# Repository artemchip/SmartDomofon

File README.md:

# Умная абонентская трубка для аналоговых домофонов
Авто-открытие, воспроизведение аудио в линию вызова
Устройство:

UI:

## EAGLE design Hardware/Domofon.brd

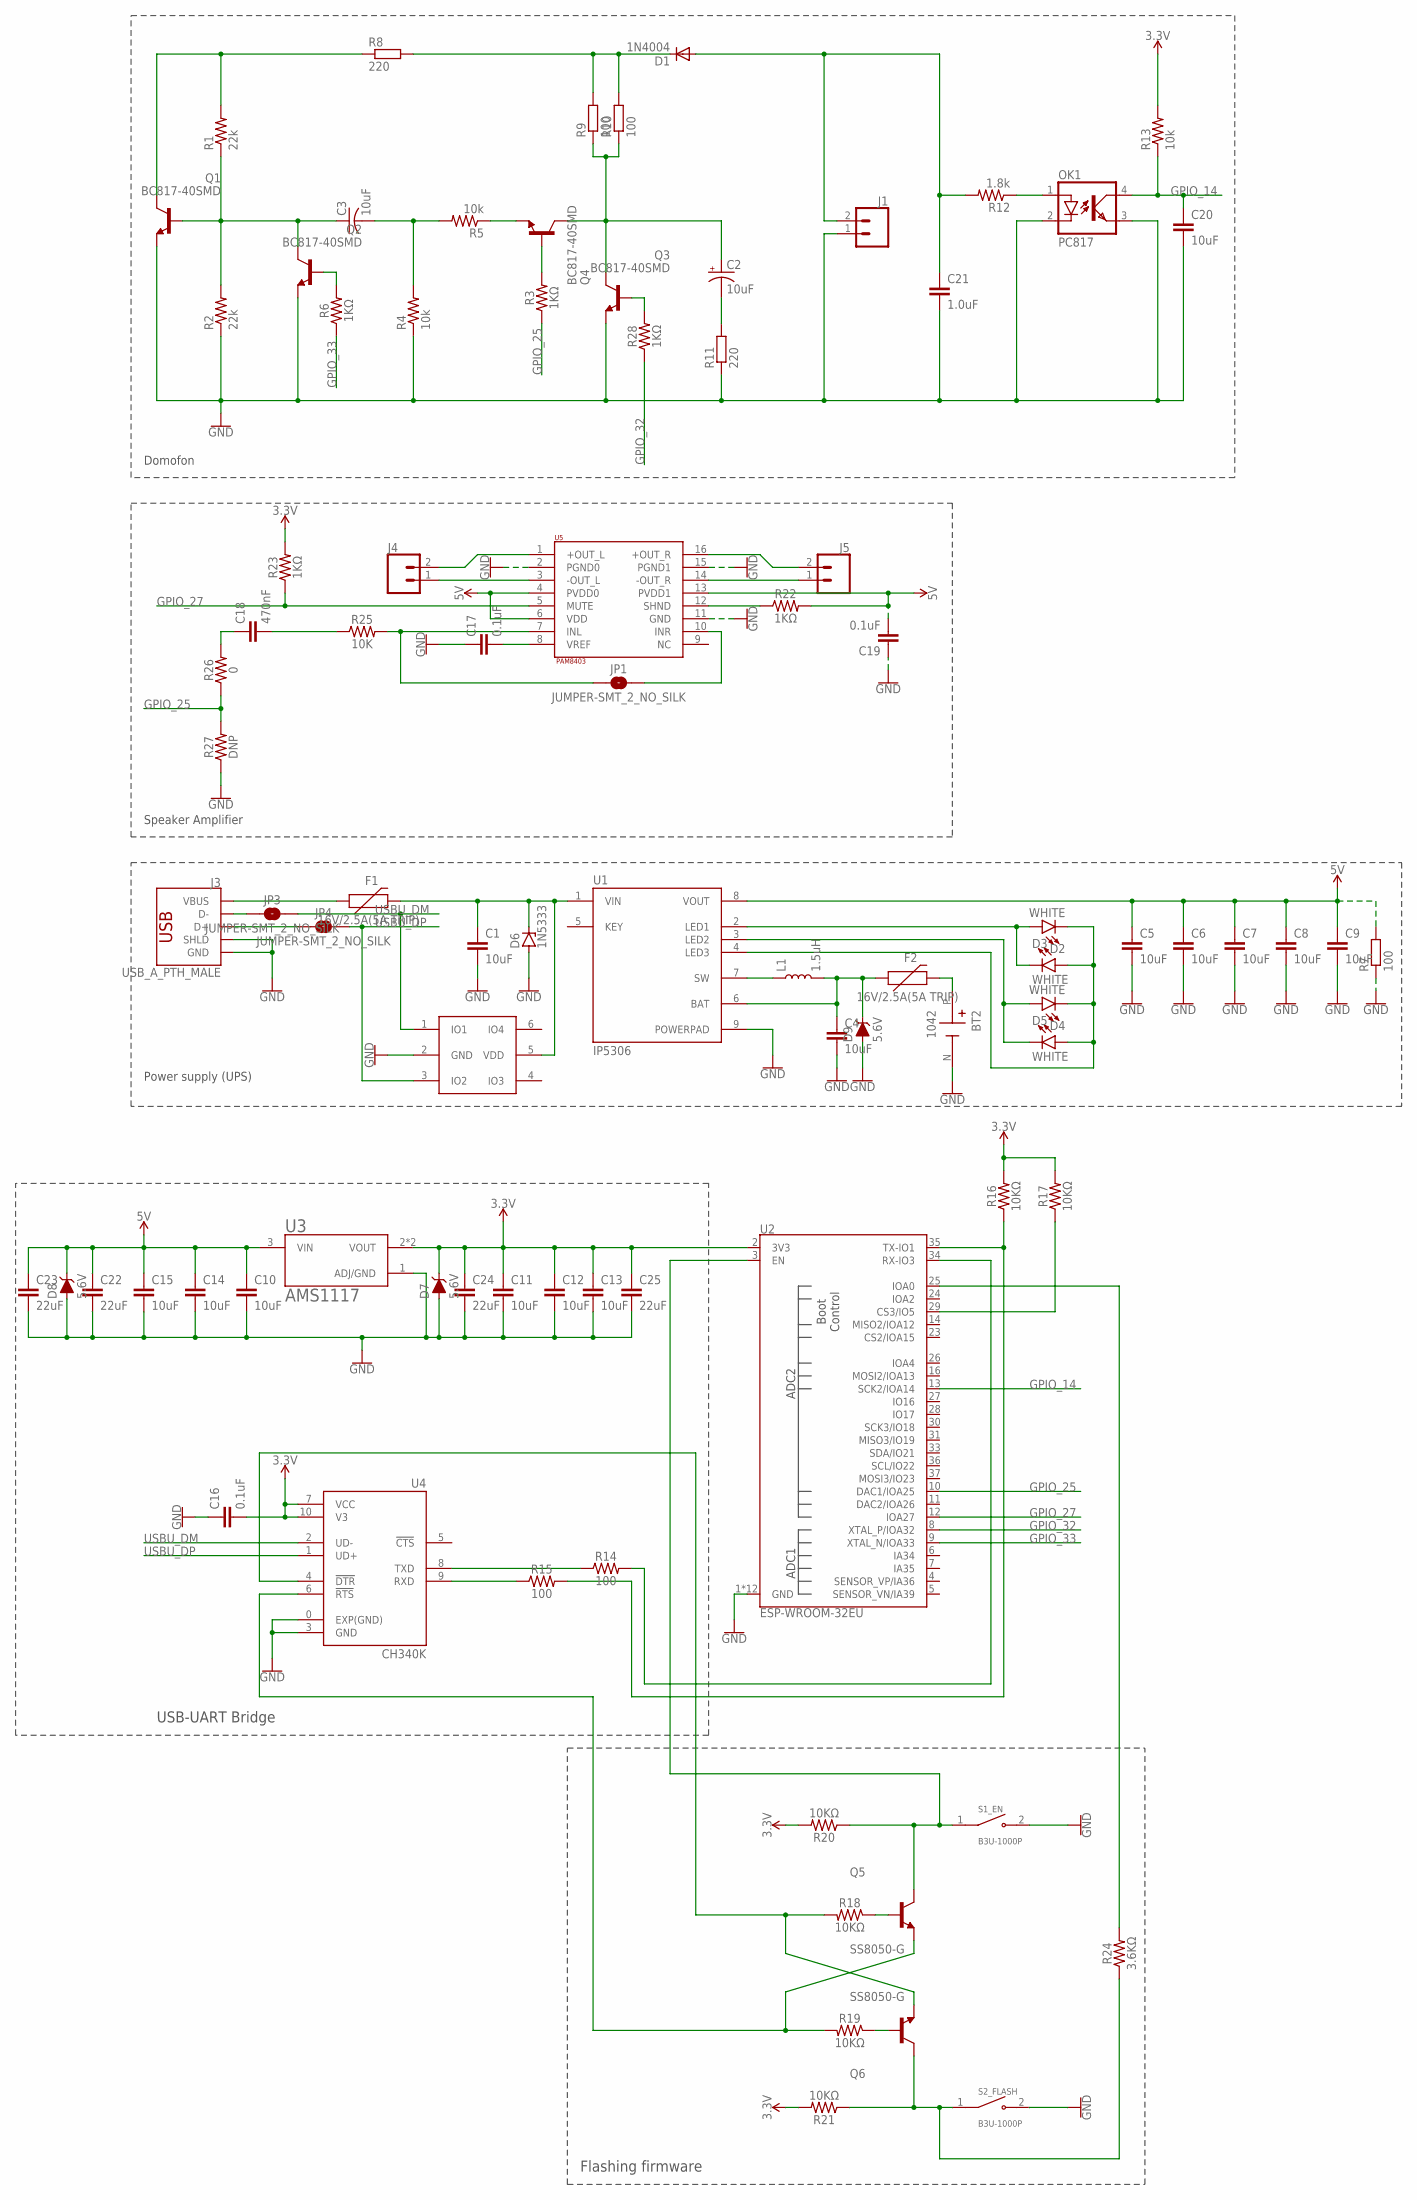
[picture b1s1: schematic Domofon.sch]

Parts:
BT2: 1042; BAT_1042
C1, C4, C5, C6, C7, C8, C9, C10, C11, C12, C13, C14, C15, C20: 10uF; 0603
C2: 10uF; CPOL-RADIAL-2.5MM-5MM
C3: 10uF; C025-024X044
C16, C17, C19: 0.1uF; 0402
C18: 470nF; 0402
C21: 1.0uF; 0603
C22, C23, C24, C25: 22uF; 1206
D1: 1N4004; DO41-10
D2, D3, D4, D5: WHITE; LED-0603
D6: 1N5333; C1702-15
D7, D8, D9: 5.6V; SOD-323
F1, F2: 16V/2.5A(5A TRIP); 1812
J1: CONN_02POLAR_LOCK; MOLEX-1X2_LOCK
J3: USB_A_PTH_MALE; USB-A-H
J4, J5: CONN_02LOCK_LONGPADS; 1X02_LOCK_LONGPADS
JP1, JP3, JP4: JUMPER-SMT_2_NO_SILK; SMT-JUMPER_2_NO_SILK
L1: 1.5uH; INDUCTOR_2X2
OK1: PC817; DIL04
Q1, Q2, Q3, Q4: BC817-40SMD; SOT23-BEC
Q5, Q6: SS8050-G; TRANS_SS8050-G
R1, R2: 22k; 0603
R3, R6, R22, R23, R28: 1KΩ; 0402-TIGHT
R4, R5, R13: 10k; 0603
R7, R9, R10: 100; 0411/15
R8, R11: 220; 0411/15
R12: 1.8k; 0603
R14, R15: 100; 0402-TIGHT
R16, R17, R18, R19, R20, R21: 10KΩ; 0402-TIGHT
R24: 3.6KΩ; 0402-TIGHT
R25: 10K; 0402-TIGHT
R26: 0; 0603
R27: DNP; 0603
S1_EN, S2_FLASH: B3U-1000P; SW_B3U-1000P
U1: IP5306; SOP127P600X165-9N
U2: ESP-WROOM-32EU
U3: AMS1117; SOT229P700X180-4N
U4: CH340K; SOP100P600X160-11N
U5: PAM8403; SOP-16
U6: AZC099-04S; SOT95P275X110-6N

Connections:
3.3V: C11.1, C12.1, C13.1, C16.2, C24.1, C25.1, D7.C, R13.2, R16.2, R17.2, R20.2, R21.2, R23.2, U2.2 (3V3), U3.2 (VOUT), U3.4 (VOUT), U4.7 (VCC), U4.10 (V3)
5V: C5.1, C6.1, C7.1, C8.1, C9.1, C10.1, C14.1, C15.1, C19.2, C22.1, C23.1, D8.C, R7.2, R22.2, U1.8 (VOUT), U3.3 (VIN), U5.4 (PVDD0), U5.6 (VDD), U5.13 (PVDD1)
GND: BT2.N (NEG), C1.2, C4.2, C5.2, C6.2, C7.2, C8.2, C9.2, C10.2, C11.2, C12.2, C13.2, C14.2, C15.2, C16.1, C17.1, C19.1, C20.2, C21.2, C22.2, C23.2, C24.2, C25.2, D6.A, D7.A, D8.A, D9.A, J1.1, J3.GND, J3.SHLD1 (SHLD), J3.SHLD2 (SHLD), OK1.2 (C), OK1.3 (EMIT), Q1.E, Q2.E, Q3.E, R2.1, R4.1, R7.1, R11.1, R27.1, S1_EN.2, S2_FLASH.2, U1.9 (POWERPAD), U2.1 (GND), U2.15 (GND), U2.38 (GND), U2.GND, U2.GNDT1 (GND), U2.GNDT2 (GND), U2.GNDT3 (GND), U2.GNDT4 (GND), U2.GNDT5 (GND), U2.GNDT6 (GND), U2.GNDT7 (GND), U2.GNDT8 (GND), U3.1 (ADJ/GND), U4.0 (EXP(GND)), U4.3 (GND), U5.2 (PGND0), U5.11 (GND), U5.15 (PGND1), U6.2 (GND)
GPIO_14: C20.1, OK1.4 (COL), R13.1, U2.13 (SCK2/IOA14)
GPIO_25: R3.1, R26.1, R27.2, U2.10 (DAC1/IOA25)
GPIO_27: R23.1, U2.12 (IOA27), U5.5 (MUTE)
GPIO_32: R28.1, U2.8 (XTAL_P/IOA32)
GPIO_33: R6.1, U2.9 (XTAL_N/IOA33)
unnamed: C3.1, Q1.B, Q2.C, R1.1, R2.2
unnamed: OK1.1 (A), R12.1
unnamed: Q1.C, R1.2, R8.1
unnamed: Q2.B, R6.2
unnamed: C1.1, D6.C, F1.2, U1.1 (VIN), U6.5 (VDD)
unnamed: C3.2, R4.2, R5.2
unnamed: D2.A, D3.C, U1.2 (LED1)
unnamed: Q4.E, R5.1
unnamed: Q4.B, R3.2
unnamed: D2.C, D3.A, D4.C, D5.A, U1.4 (LED3)
unnamed: C2.1 (+), Q3.C, Q4.C, R9.1, R10.1
unnamed: Q3.B, R28.2
unnamed: D4.A, D5.C, U1.3 (LED2)
unnamed: Q6.2 (E), R18.2, U4.4 (!DTR)
unnamed: D1.C, R8.2, R9.2, R10.2
unnamed: C2.2 (-), R11.2
unnamed: L1.P$1 (1), U1.7 (SW)
unnamed: C21.1, D1.A, J1.2, R12.2
unnamed: C4.1, D9.C, F2.1, L1.P$2 (2), U1.6 (BAT)
unnamed: Q5.2 (E), R19.2, U4.6 (!RTS)
unnamed: J3.D-, JP3.1
unnamed: J3.D+, JP4.1
unnamed: R15.2, R16.1, U2.35 (TX-IO1)
unnamed: R14.2, U2.34 (RX-IO3)
unnamed: R17.1, U2.29 (CS3/IO5)
unnamed: Q6.1 (B), R19.1
unnamed: Q5.1 (B), R18.1
unnamed: R24.2, U2.25 (IOA0)
unnamed: Q5.3 (C), R20.1, S1_EN.1, U2.3 (EN)
unnamed: J4.1, U5.3 (-OUT_L)
unnamed: J4.2, U5.1 (+OUT_L)
unnamed: J5.1, U5.14 (-OUT_R)
unnamed: J5.2, U5.16 (+OUT_R)
unnamed: R22.1, U5.12 (SHND)
unnamed: Q6.3 (C), R21.1, R24.1, S2_FLASH.1
unnamed: C17.2, U5.8 (VREF)
unnamed: JP1.1, R25.2, U5.7 (INL)
unnamed: R14.1, U4.8 (TXD)
unnamed: R15.1, U4.9 (RXD)
unnamed: C18.2, R25.1
unnamed: JP1.2, U5.10 (INR)
unnamed: C18.1, R26.2
unnamed: F1.1, J3.VBUS
unnamed: BT2.P (POS), F2.2
USBU_DM: JP3.2, U4.2 (UD-), U6.1 (IO1)
USBU_DP: JP4.2, U4.1 (UD+), U6.3 (IO2)

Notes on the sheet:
Flashing firmware
USB-UART Bridge
Power supply (UPS)
Domofon
Speaker Amplifier

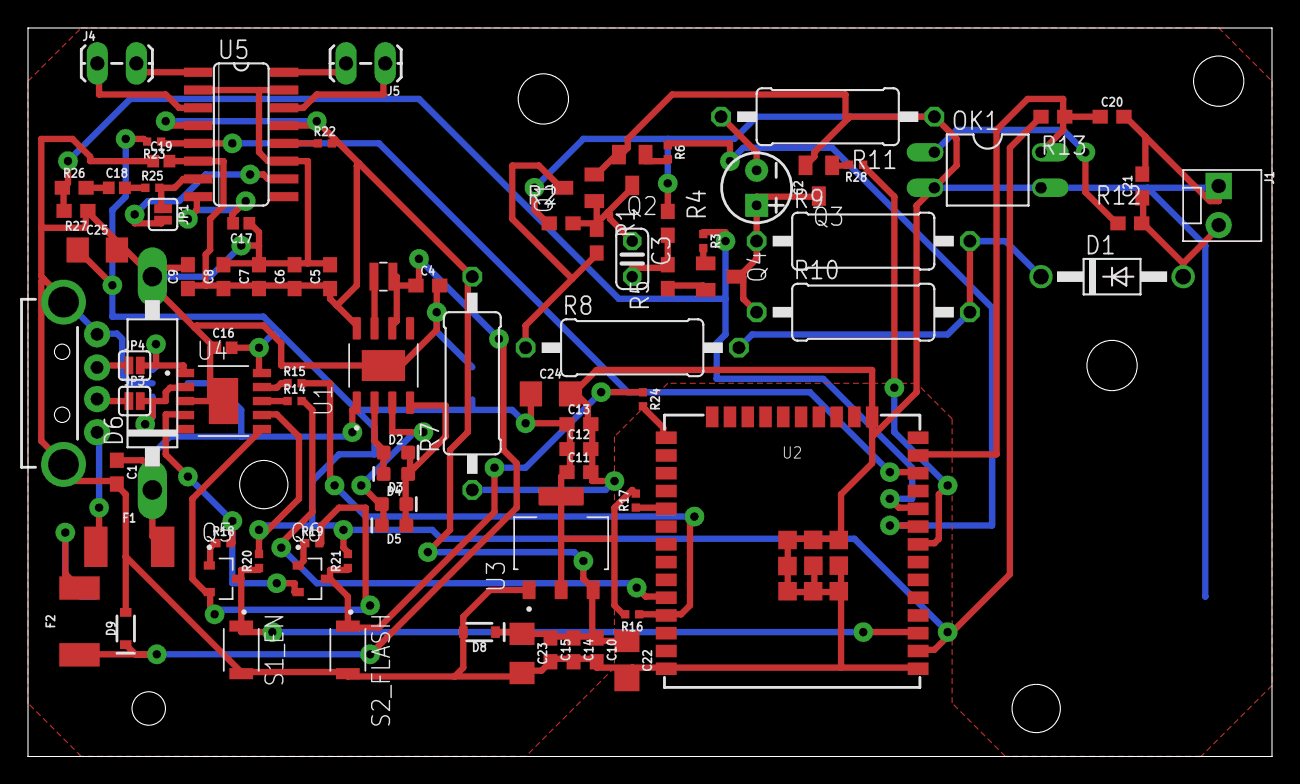
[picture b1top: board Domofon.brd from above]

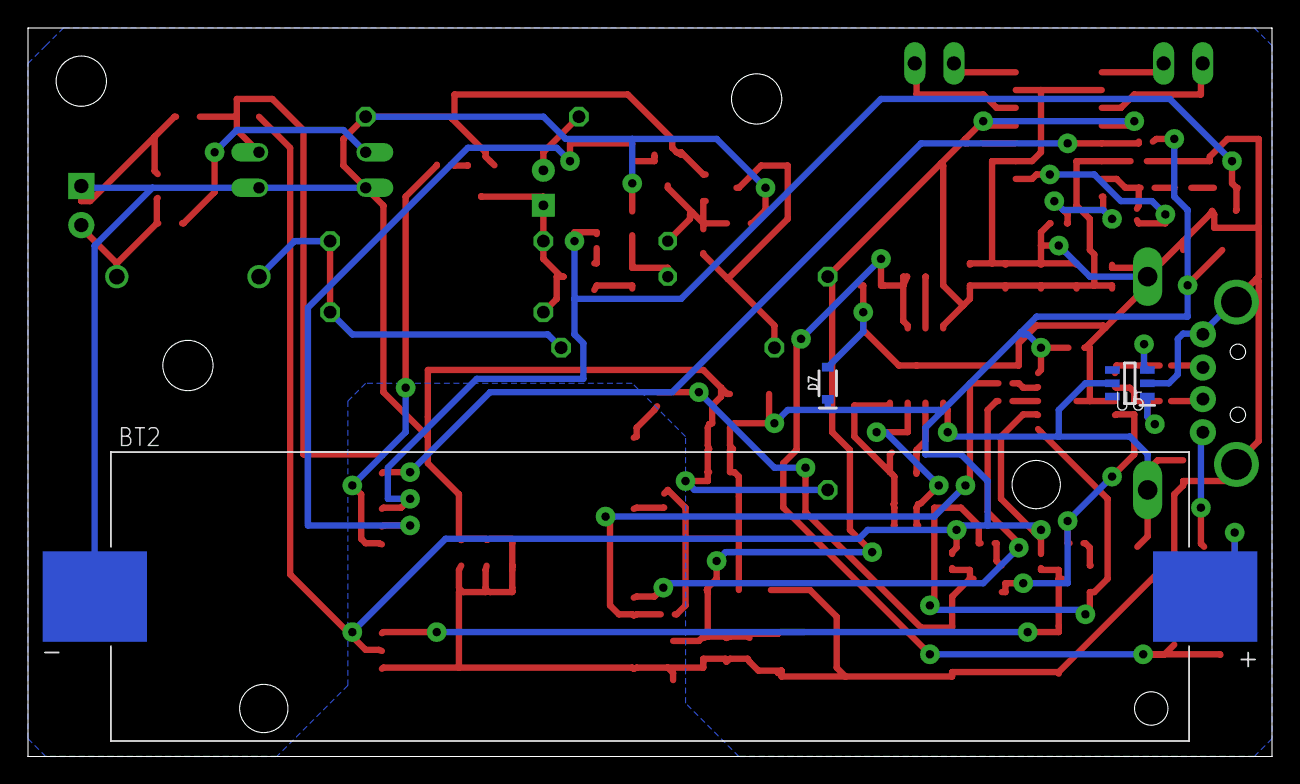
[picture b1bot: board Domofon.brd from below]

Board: 2 copper layers, 88.9 x 52.1 mm, 88 parts (3 on the bottom side), 54 nets.

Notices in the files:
parts and their libraries:
SparkFun-Capacitors: Licensing: Creative Commons ShareAlike 4.0 International - https://creativecommons.org/licenses/by-sa/4.0
